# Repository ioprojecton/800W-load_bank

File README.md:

# 800W Load bank for generators

800W load bank for load test 1KW generators.
2steps each 400W via switch

## Authors

- [@ioprojecton](https://www.github.com/ioprojecton)

## Screenshots

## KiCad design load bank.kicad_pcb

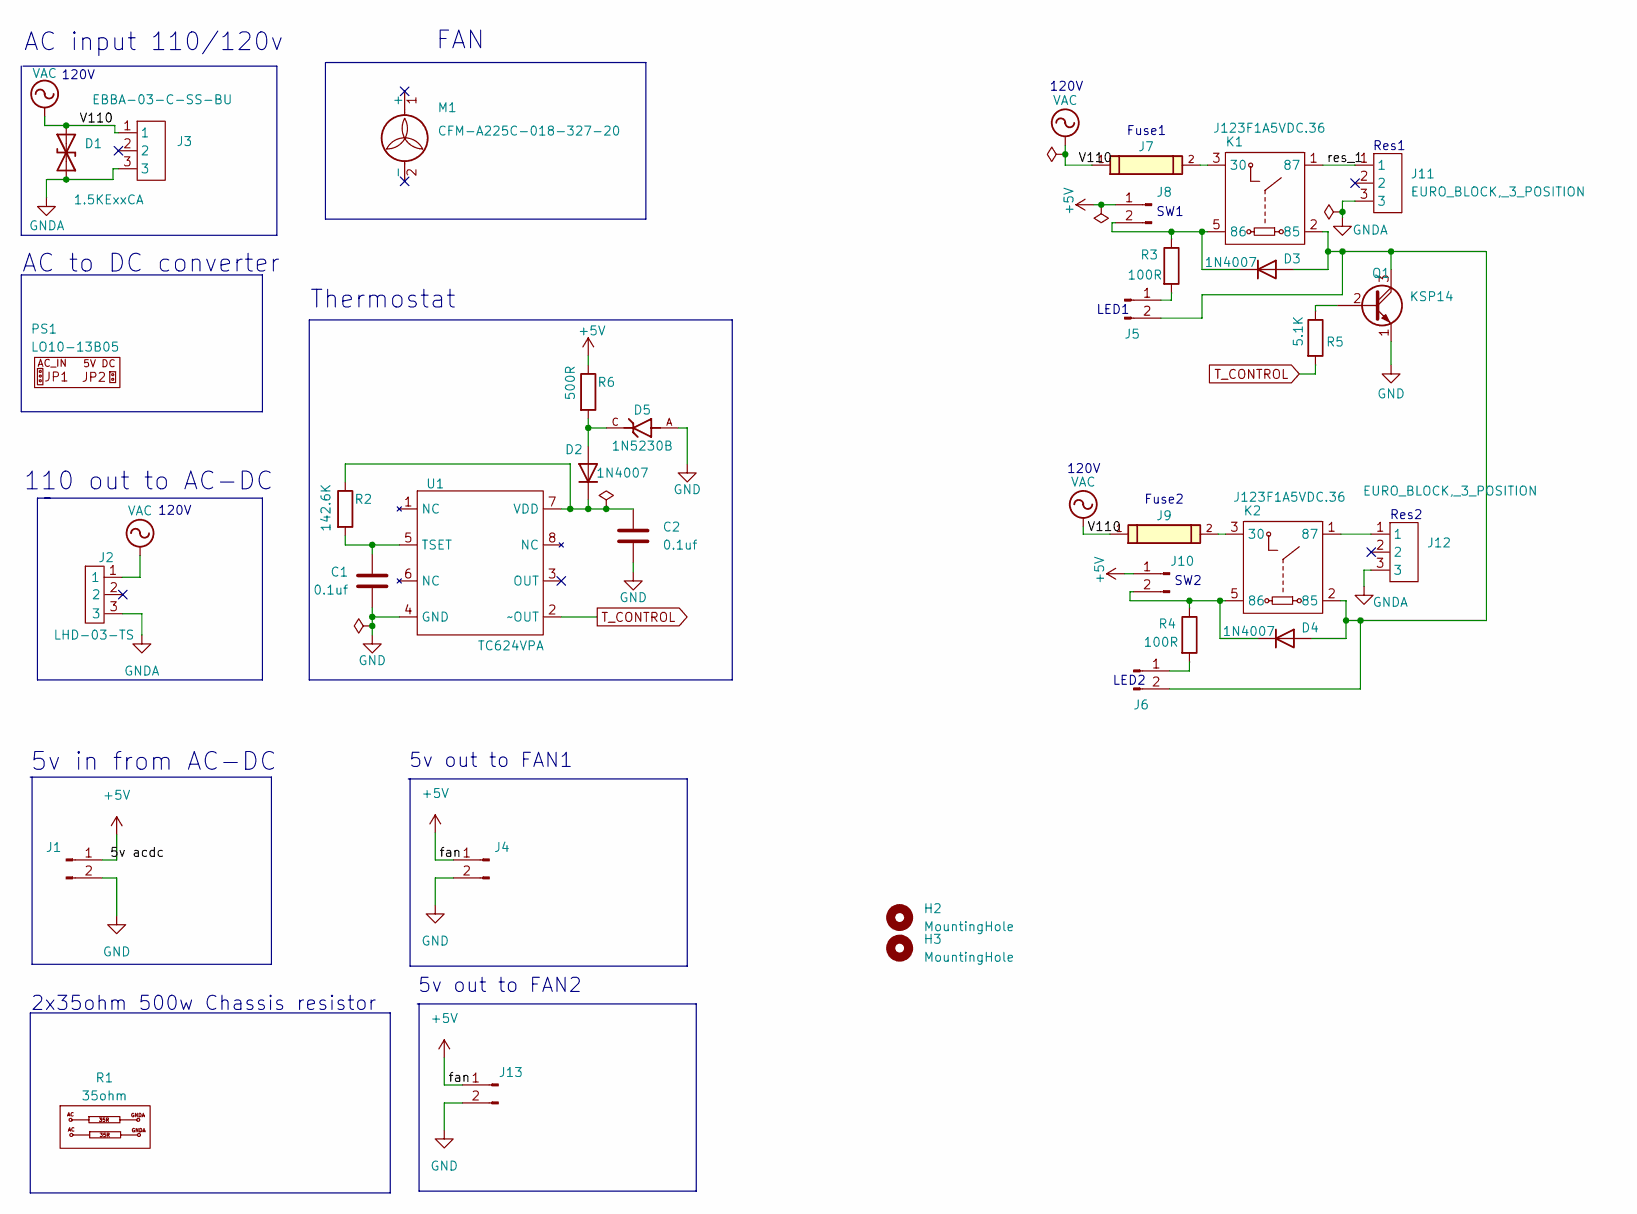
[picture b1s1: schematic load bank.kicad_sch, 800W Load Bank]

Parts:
C1, C2: 0.1uf; C_Disc_D3.0mm_W1.6mm_P2.50mm
D1: 1.5KExxCA; D_DO-201AE_P15.24mm_Horizontal
D2, D3, D4: 1N4007; D_DO-41_SOD81_P10.16mm_Horizontal
D5: 1N5230B; DIOAD928W47L399D179; PARTREV G1804
H2, H3: MountingHole; MountingHole_3.2mm_M3_DIN965_Pad_TopBottom
J1, J4, J8, J10, J13: 25SH-B-02-TS; JST_EH_B2B-EH-A_1x02_P2.50mm_Vertical
J2: LHD-03-TS; JST_VH_B3P-VH-FB-B_1x03_P3.96mm_Vertical
J3: EBBA-03-C-SS-BU; EURO_BLOCK,_3_POSITION
J5, J6: Conn_01x02_Male; JST_EH_B2B-EH-A_1x02_P2.50mm_Vertical
J7, J9: 696101000002; PART-NUMBER 696101000002
J11, J12: EURO_BLOCK,_3_POSITION
K1, K2: J123F1A5VDC.36; Relay_SPST_SANYOU_SRD_Series_Form_A
M1: CFM-A225C-018-327-20
PS1: LO10-13B05
Q1: KSP14; KSP13
R1: 35ohm
R2: 142.6K; R_Axial_DIN0207_L6.3mm_D2.5mm_P7.62mm_Horizontal
R3, R4: 100R; R_Axial_DIN0207_L6.3mm_D2.5mm_P10.16mm_Horizontal
R5: 5.1K; R_Axial_DIN0207_L6.3mm_D2.5mm_P10.16mm_Horizontal
R6: 500R; R_Axial_DIN0207_L6.3mm_D2.5mm_P7.62mm_Horizontal
U1: TC624VPA; DIP-8_300_ELL

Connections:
+5V: J1.1, J4.1, J8.1, J10.1, J13.1, R6.1
/res_1: J11.1, K1.1 (87)
GND: C1.1, C2.2, D5.A, J1.2, J4.2, J13.2, Q1.1 (E), U1.4 (GND)
GNDA: D1.1 (A1), J2.3, J3.3, J11.3, J12.3
unnamed: D2.2 (A), D5.C, R6.2
unnamed: C2.1, D2.1 (K), R2.1, U1.7 (VDD)
unnamed: D3.2 (A), D4.2 (A), J5.2, J6.2, K1.2 (85), K2.2 (85), Q1.3 (C)
unnamed: D3.1 (K), J8.2, K1.5 (86), R3.1
unnamed: D4.1 (K), J10.2, K2.5 (86), R4.1
unnamed: J5.1, R3.2
unnamed: J6.1, R4.2
unnamed: J7.2, K1.3 (30)
unnamed: J9.2, K2.3 (30)
unnamed: J12.1, K2.1 (87)
unnamed: Q1.2 (B), R5.1
unnamed: C1.2, R2.2, U1.5 (TSET)
T_CONTROL: R5.2, U1.2 (~OUT)
VAC: D1.2 (A2), J2.1, J3.1, J7.1, J9.1

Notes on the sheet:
110 out to AC-DC
SW1
Thermostat
AC to DC converter
Res1
SW2
LED1
Res2
AC input 110/120v
120V
2x35ohm 500w Chassis resistor
5v out to FAN2
LED2
Fuse1
5v in from AC-DC
5v out to FAN1
Fuse2
FAN

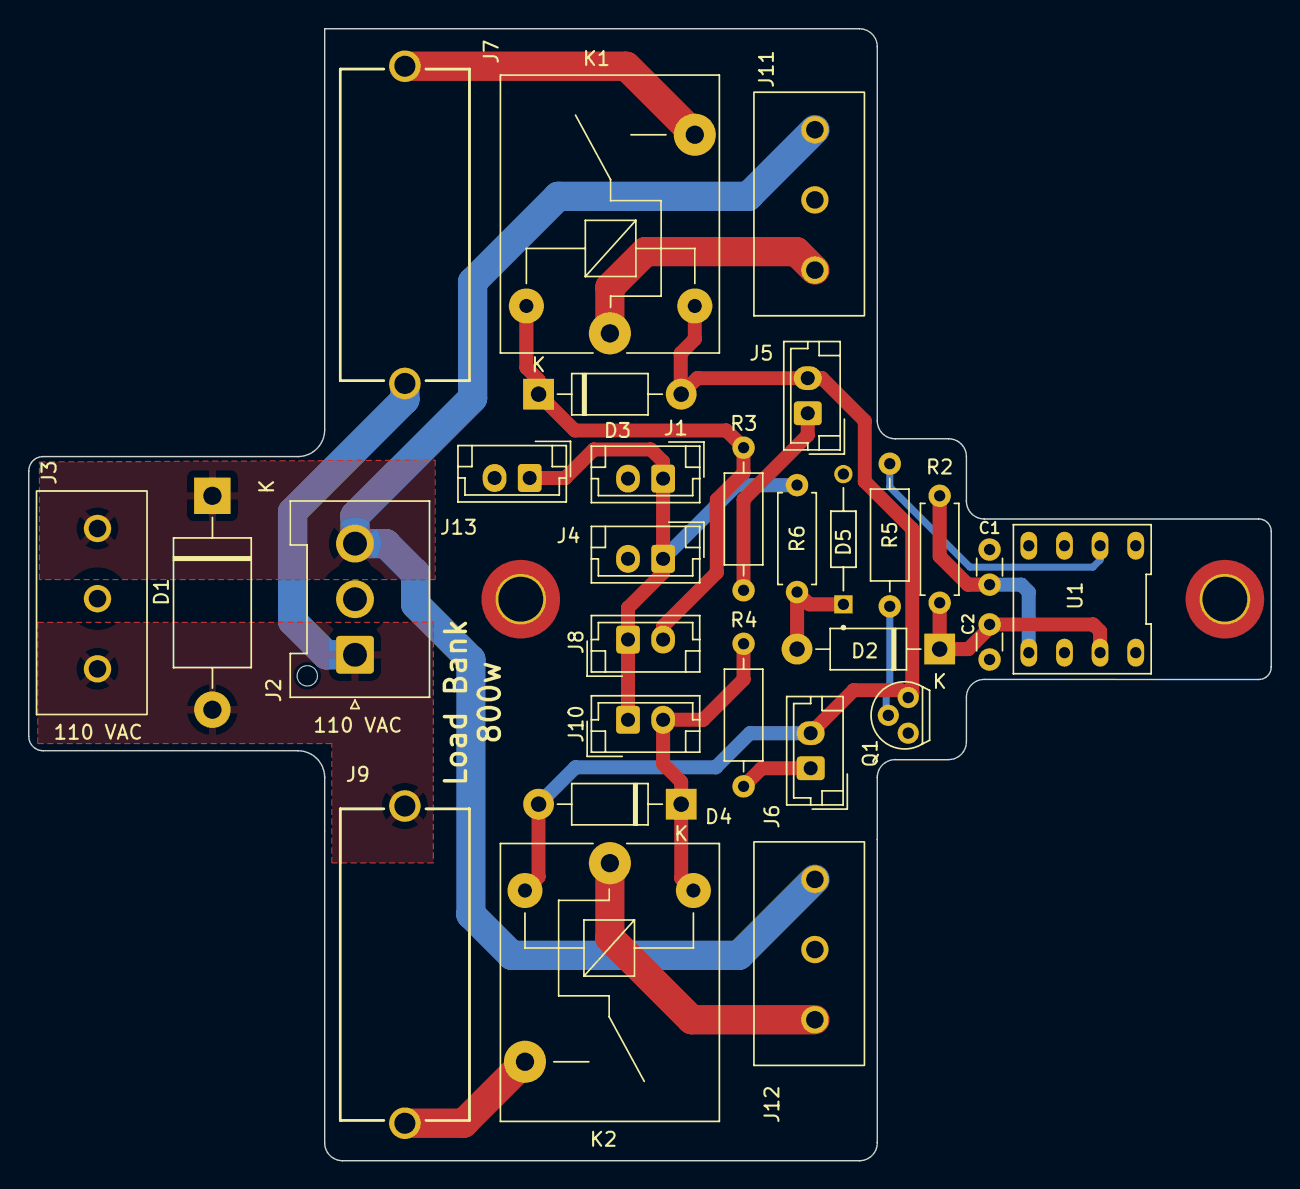
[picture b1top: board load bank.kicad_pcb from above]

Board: 2 copper layers, 88.5 x 80.6 mm, 31 parts (0 on the bottom side), 18 nets.

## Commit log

2023-02-07 added BOM
2023-02-07 added 3d pics
2023-02-07 added schematic jpg
2023-02-07 added README
2023-02-07 added backside of pcb
2023-02-17 added second fan connector for parallel connection
2023-02-17 updated pcb with fan2 connector
2023-02-17 added 4.7v zener + resistor to keep TC624 voltage in range
2023-02-17 updated pcb layout with zener and resistor
2023-02-21 repositioned mounting hole
